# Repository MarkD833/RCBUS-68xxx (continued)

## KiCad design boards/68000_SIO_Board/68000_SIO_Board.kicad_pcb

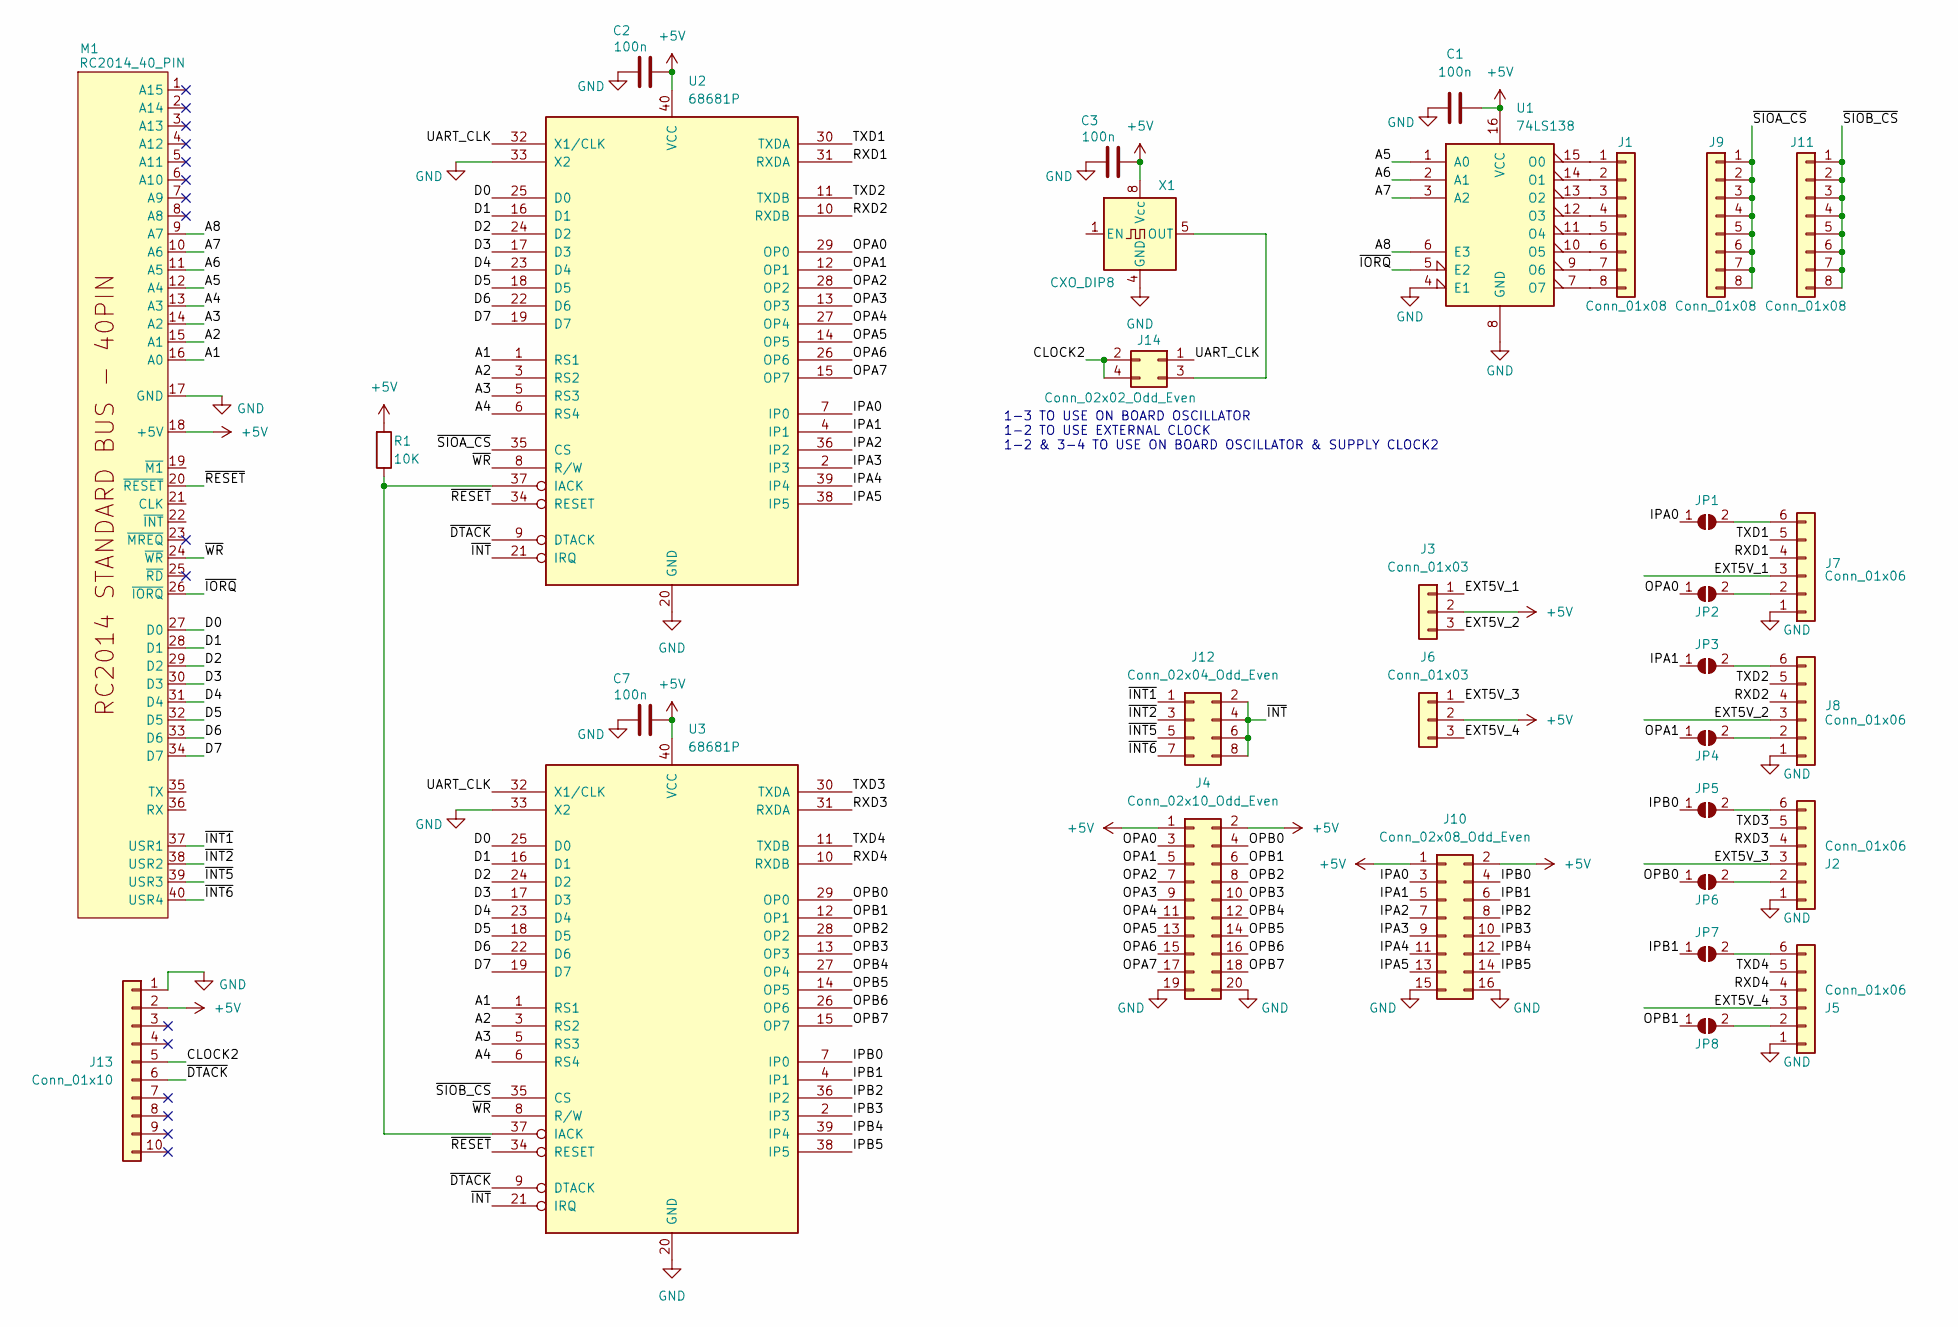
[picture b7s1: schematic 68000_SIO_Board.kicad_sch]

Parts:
C1, C2, C3, C7: 100n; C_Disc_D5.0mm_W2.5mm_P2.50mm
J1, J9, J11: Conn_01x08; PinHeader_1x08_P2.54mm_Vertical
J2, J5, J7, J8: Conn_01x06; PinSocket_1x06_P2.54mm_Horizontal
J3, J6: Conn_01x03; PinHeader_1x03_P2.54mm_Vertical
J4: Conn_02x10_Odd_Even; PinHeader_2x10_P2.54mm_Horizontal
J10: Conn_02x08_Odd_Even; PinHeader_2x08_P2.54mm_Horizontal
J12: Conn_02x04_Odd_Even; PinHeader_2x04_P2.54mm_Vertical
J13: Conn_01x10; PinHeader_1x10_P2.54mm_Vertical
J14: Conn_02x02_Odd_Even; PinHeader_2x02_P2.54mm_Vertical
JP1, JP2, JP3, JP4, JP5, JP6, JP7, JP8: SolderJumper; SolderJumper-2_P1.3mm_Open_Pad1.0x1.5mm
M1: RC2014_40_PIN; RC2014_STD_40_PIN
R1: 10K; R_Axial_DIN0207_L6.3mm_D2.5mm_P7.62mm_Horizontal
U1: 74LS138; DIP-16_W7.62mm_Socket
U2, U3: 68681P; DIP-40_W15.24mm_Socket
X1: CXO_DIP8; Oscillator_DIP-8

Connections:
+5V: C1.2, C2.2, C3.2, C7.2, J3.2, J4.1, J4.2, J6.2, J10.1, J10.2, J13.2, M1.18 (+5V), R1.2, U1.16 (VCC), U2.40 (VCC), U3.40 (VCC), X1.8 (Vcc)
/A1: M1.16 (A0), U2.1 (RS1), U3.1 (RS1)
/A2: M1.15 (A1), U2.3 (RS2), U3.3 (RS2)
/A3: M1.14 (A2), U2.5 (RS3), U3.5 (RS3)
/A4: M1.13 (A3), U2.6 (RS4), U3.6 (RS4)
/A5: M1.12 (A4), U1.1 (A0)
/A6: M1.11 (A5), U1.2 (A1)
/A7: M1.10 (A6), U1.3 (A2)
/A8: M1.9 (A7), U1.6 (E3)
/CLOCK2: J13.5, J14.2, J14.4
/D0: M1.27 (D0), U2.25 (D0), U3.25 (D0)
/D1: M1.28 (D1), U2.16 (D1), U3.16 (D1)
/D2: M1.29 (D2), U2.24 (D2), U3.24 (D2)
/D3: M1.30 (D3), U2.17 (D3), U3.17 (D3)
/D4: M1.31 (D4), U2.23 (D4), U3.23 (D4)
/D5: M1.32 (D5), U2.18 (D5), U3.18 (D5)
/D6: M1.33 (D6), U2.22 (D6), U3.22 (D6)
/D7: M1.34 (D7), U2.19 (D7), U3.19 (D7)
/EXT5V_1: J3.1, J7.3
/EXT5V_2: J3.3, J8.3
/EXT5V_3: J2.3, J6.1
/EXT5V_4: J5.3, J6.3
/IPA0: J10.3, JP1.1 (A), U2.7 (IP0)
/IPA1: J10.5, JP3.1 (A), U2.4 (IP1)
/IPA2: J10.7, U2.36 (IP2)
/IPA3: J10.9, U2.2 (IP3)
/IPA4: J10.11, U2.39 (IP4)
/IPA5: J10.13, U2.38 (IP5)
/IPB0: J10.4, JP5.1 (A), U3.7 (IP0)
/IPB1: J10.6, JP7.1 (A), U3.4 (IP1)
/IPB2: J10.8, U3.36 (IP2)
/IPB3: J10.10, U3.2 (IP3)
/IPB4: J10.12, U3.39 (IP4)
/IPB5: J10.14, U3.38 (IP5)
/OPA0: J4.3, JP2.1 (A), U2.29 (OP0)
/OPA1: J4.5, JP4.1 (A), U2.12 (OP1)
/OPA2: J4.7, U2.28 (OP2)
/OPA3: J4.9, U2.13 (OP3)
/OPA4: J4.11, U2.27 (OP4)
/OPA5: J4.13, U2.14 (OP5)
/OPA6: J4.15, U2.26 (OP6)
/OPA7: J4.17, U2.15 (OP7)
/OPB0: J4.4, JP6.1 (A), U3.29 (OP0)
/OPB1: J4.6, JP8.1 (A), U3.12 (OP1)
/OPB2: J4.8, U3.28 (OP2)
/OPB3: J4.10, U3.13 (OP3)
/OPB4: J4.12, U3.27 (OP4)
/OPB5: J4.14, U3.14 (OP5)
/OPB6: J4.16, U3.26 (OP6)
/OPB7: J4.18, U3.15 (OP7)
/RXD1: J7.4, U2.31 (RXDA)
/RXD2: J8.4, U2.10 (RXDB)
/RXD3: J2.4, U3.31 (RXDA)
/RXD4: J5.4, U3.10 (RXDB)
/TXD1: J7.5, U2.30 (TXDA)
/TXD2: J8.5, U2.11 (TXDB)
/TXD3: J2.5, U3.30 (TXDA)
/TXD4: J5.5, U3.11 (TXDB)
/UART_CLK: J14.1, U2.32 (X1/CLK), U3.32 (X1/CLK)
/~DTACK: J13.6, U2.9 (DTACK), U3.9 (DTACK)
/~INT1: J12.1, M1.37 (USR1)
/~INT2: J12.3, M1.38 (USR2)
/~INT5: J12.5, M1.39 (USR3)
/~INT6: J12.7, M1.40 (USR4)
/~INT: J12.2, J12.4, J12.6, J12.8, U2.21 (IRQ), U3.21 (IRQ)
/~IORQ: M1.26 (~IORQ), U1.5 (E2)
/~RESET: M1.20 (~RESET), U2.34 (RESET), U3.34 (RESET)
/~SIOA_CS: J9.1, J9.2, J9.3, J9.4, J9.5, J9.6, J9.7, J9.8, U2.35 (CS)
/~SIOB_CS: J11.1, J11.2, J11.3, J11.4, J11.5, J11.6, J11.7, J11.8, U3.35 (CS)
/~WR: M1.24 (~WR), U2.8 (R/W), U3.8 (R/W)
GND: C1.1, C2.1, C3.1, C7.1, J2.1, J4.19, J4.20, J5.1, J7.1, J8.1, J10.15, J10.16, J13.1, M1.17 (GND), U1.4 (E1), U1.8 (GND), U2.20 (GND), U2.33 (X2), U3.20 (GND), U3.33 (X2), X1.4 (GND)
unnamed: J1.1, U1.15 (O0)
unnamed: J1.2, U1.14 (O1)
unnamed: J1.3, U1.13 (O2)
unnamed: J1.4, U1.12 (O3)
unnamed: J1.5, U1.11 (O4)
unnamed: J1.6, U1.10 (O5)
unnamed: J1.7, U1.9 (O6)
unnamed: J1.8, U1.7 (O7)
unnamed: J2.2, JP6.2 (B)
unnamed: J2.6, JP5.2 (B)
unnamed: J5.2, JP8.2 (B)
unnamed: J5.6, JP7.2 (B)
unnamed: J7.2, JP2.2 (B)
unnamed: J7.6, JP1.2 (B)
unnamed: J8.2, JP4.2 (B)
unnamed: J8.6, JP3.2 (B)
unnamed: J14.3, X1.5 (OUT)
unnamed: R1.1, U2.37 (IACK), U3.37 (IACK)

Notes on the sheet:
1-3 TO USE ON BOARD OSCILLATOR 1-2 TO USE EXTERNAL CLOCK 1-2 & 3-4 TO USE ON BOARD OSCILLATOR & SUPPLY CLOCK2

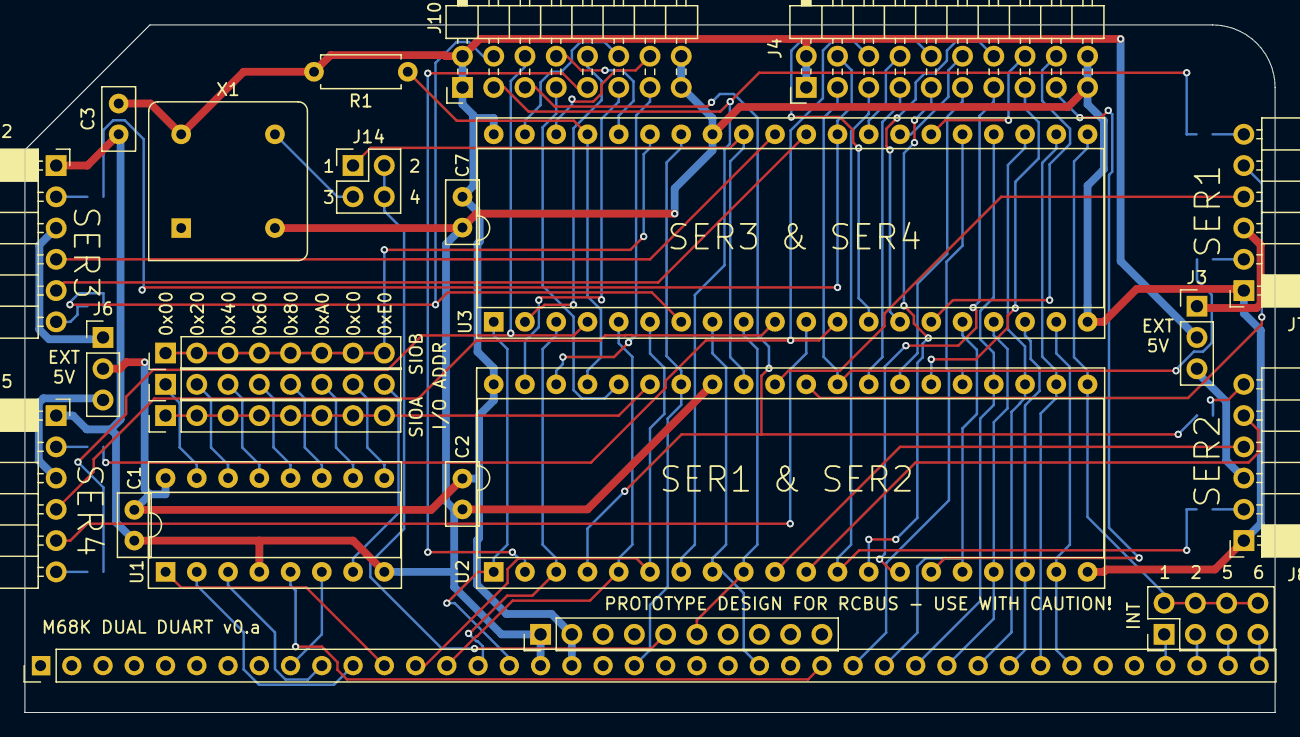
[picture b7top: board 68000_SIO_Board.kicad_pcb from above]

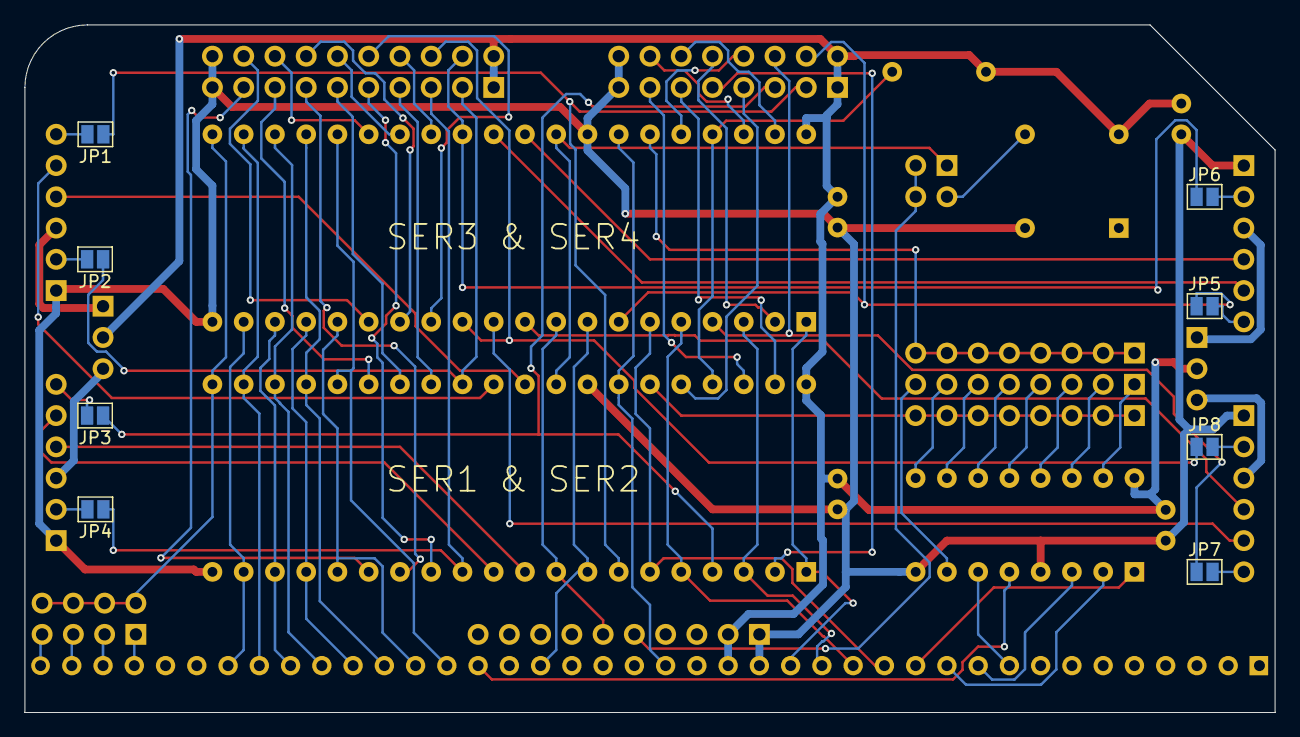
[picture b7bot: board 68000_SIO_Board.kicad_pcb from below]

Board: 2 copper layers, 101.6 x 55.9 mm, 32 parts (8 on the bottom side), 89 nets.

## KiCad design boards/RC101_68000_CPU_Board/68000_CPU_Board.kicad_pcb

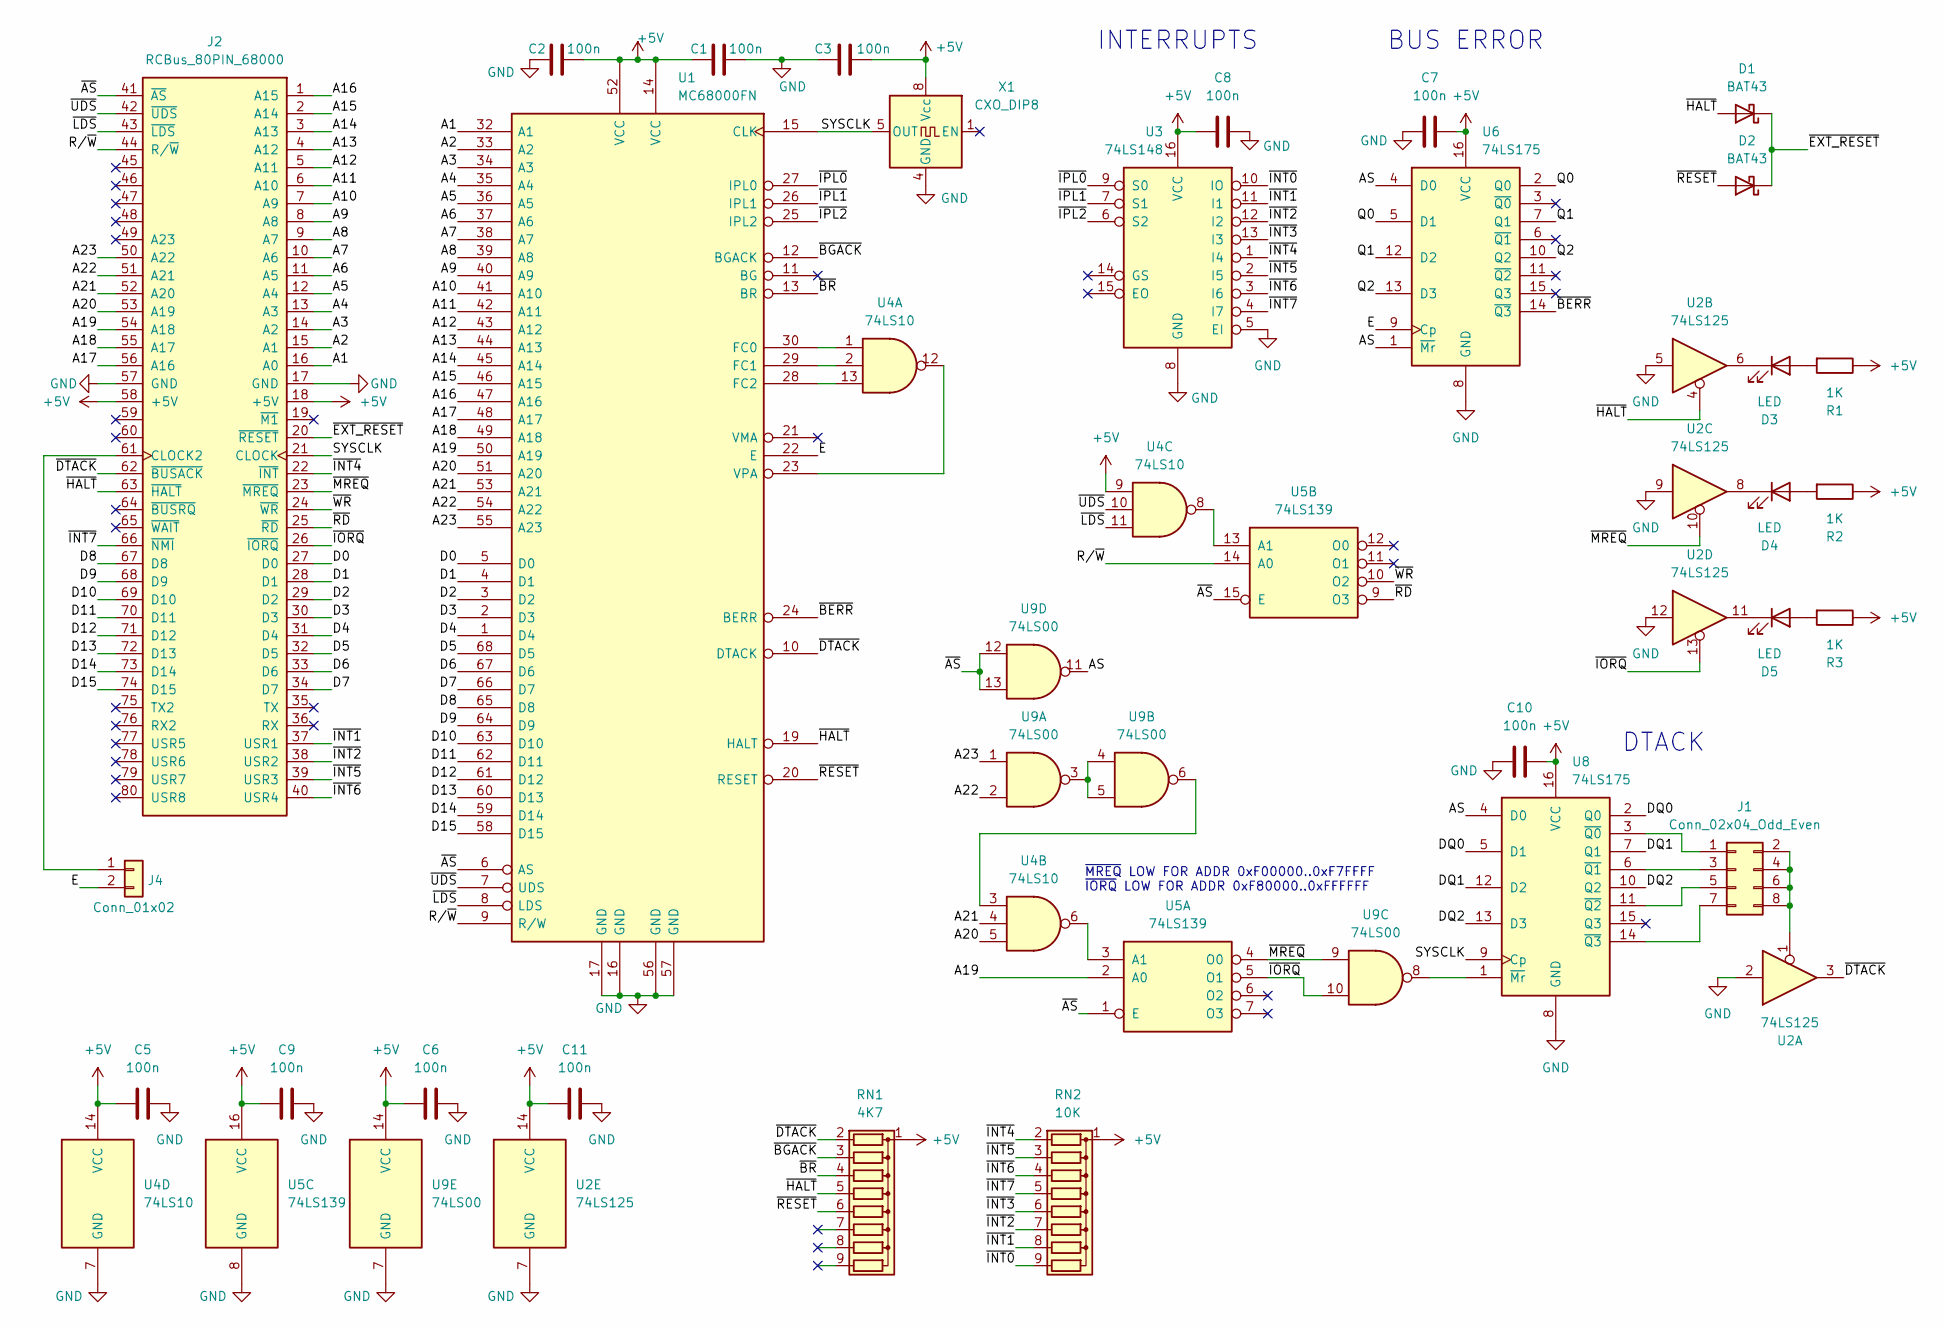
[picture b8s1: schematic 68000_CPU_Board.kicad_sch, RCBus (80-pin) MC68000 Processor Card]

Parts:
C1, C2, C3, C5, C6, C7, C8, C9, C10, C11: 100n; C_Disc_D5.0mm_W2.5mm_P2.50mm
D1, D2: BAT43; D_DO-35_SOD27_P7.62mm_Horizontal
D3, D4, D5: LED; LED_D3.0mm
J1: Conn_02x04_Odd_Even; PinHeader_2x04_P2.54mm_Vertical
J2: RCBus_80PIN_68000; RCBus_80p_Medium
J4: Conn_01x02; PinHeader_1x02_P2.54mm_Vertical
R1, R2, R3: 1K; R_Axial_DIN0207_L6.3mm_D2.5mm_P7.62mm_Horizontal
RN1: 4K7; R_Array_SIP9
RN2: 10K; R_Array_SIP9
U1: MC68000FN; PLCC-68_THT-Socket
U2: 74LS125; DIP-14_W7.62mm_Socket
U3: 74LS148; DIP-16_W7.62mm_Socket
U4: 74LS10; DIP-14_W7.62mm_Socket
U5: 74LS139; DIP-16_W7.62mm_Socket
U6, U8: 74LS175; DIP-16_W7.62mm_Socket
U9: 74LS00; DIP-14_W7.62mm_Socket
X1: CXO_DIP8; Oscillator_DIP-8

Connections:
+5V: C1.1, C2.2, C3.2, C5.1, C6.1, C7.2, C8.1, C9.1, C10.2, C11.1, J2.18 (+5V), J2.58 (+5V), R1.1, R2.1, R3.1, RN1.1 (common), RN2.1 (common), U1.14 (VCC), U1.52 (VCC), U2.14 (VCC), U3.16 (VCC), U4.9, U4.14 (VCC), U5.16 (VCC), U6.16 (VCC), U8.16 (VCC), U9.14 (VCC), X1.8 (Vcc)
/A1: J2.16 (A0), U1.32 (A1)
/A2: J2.15 (A1), U1.33 (A2)
/A3: J2.14 (A2), U1.34 (A3)
/A4: J2.13 (A3), U1.35 (A4)
/A5: J2.12 (A4), U1.36 (A5)
/A6: J2.11 (A5), U1.37 (A6)
/A7: J2.10 (A6), U1.38 (A7)
/A8: J2.9 (A7), U1.39 (A8)
/A9: J2.8 (A8), U1.40 (A9)
/A10: J2.7 (A9), U1.41 (A10)
/A11: J2.6 (A10), U1.42 (A11)
/A12: J2.5 (A11), U1.43 (A12)
/A13: J2.4 (A12), U1.44 (A13)
/A14: J2.3 (A13), U1.45 (A14)
/A15: J2.2 (A14), U1.46 (A15)
/A16: J2.1 (A15), U1.47 (A16)
/A17: J2.56 (A16), U1.48 (A17)
/A18: J2.55 (A17), U1.49 (A18)
/A19: J2.54 (A18), U1.50 (A19), U5.2 (A0)
/A20: J2.53 (A19), U1.51 (A20), U4.5
/A21: J2.52 (A20), U1.53 (A21), U4.4
/A22: J2.51 (A21), U1.54 (A22), U9.2
/A23: J2.50 (A22), U1.55 (A23), U9.1
/AS: U6.1 (~Mr), U6.4 (D0), U8.4 (D0), U9.11
/D0: J2.27 (D0), U1.5 (D0)
/D1: J2.28 (D1), U1.4 (D1)
/D2: J2.29 (D2), U1.3 (D2)
/D3: J2.30 (D3), U1.2 (D3)
/D4: J2.31 (D4), U1.1 (D4)
/D5: J2.32 (D5), U1.68 (D5)
/D6: J2.33 (D6), U1.67 (D6)
/D7: J2.34 (D7), U1.66 (D7)
/D8: J2.67 (D8), U1.65 (D8)
/D9: J2.68 (D9), U1.64 (D9)
/D10: J2.69 (D10), U1.63 (D10)
/D11: J2.70 (D11), U1.62 (D11)
/D12: J2.71 (D12), U1.61 (D12)
/D13: J2.72 (D13), U1.60 (D13)
/D14: J2.73 (D14), U1.59 (D14)
/D15: J2.74 (D15), U1.58 (D15)
/DQ0: U8.2 (Q0), U8.5 (D1)
/DQ1: U8.7 (Q1), U8.12 (D2)
/DQ2: U8.10 (Q2), U8.13 (D3)
/E: J4.2, U1.22 (E), U6.9 (Cp)
/Q0: U6.2 (Q0), U6.5 (D1)
/Q1: U6.7 (Q1), U6.12 (D2)
/Q2: U6.10 (Q2), U6.13 (D3)
/R/~W: J2.44 (R/~W), U1.9 (R/W), U5.14 (A0)
/SYSCLK: J2.21 (CLOCK), U1.15 (CLK), U8.9 (Cp), X1.5 (OUT)
/~AS: J2.41 (~AS), U1.6 (AS), U5.1 (E), U5.15 (E), U9.12, U9.13
/~BERR: U1.24 (BERR), U6.14 (~Q3)
/~BGACK: RN1.3 (R2), U1.12 (BGACK)
/~BR: RN1.4 (R3), U1.13 (BR)
/~DTACK: J2.62 (~BUSACK), RN1.2 (R1), U1.10 (DTACK), U2.3
/~EXT_RESET: D1.1 (K), D2.1 (K), J2.20 (~RESET)
/~HALT: D1.2 (A), J2.63 (~HALT), RN1.5 (R4), U1.19 (HALT), U2.4
/~INT0: RN2.9 (R8), U3.10 (IO)
/~INT1: J2.37 (USR1), RN2.8 (R7), U3.11 (I1)
/~INT2: J2.38 (USR2), RN2.7 (R6), U3.12 (I2)
/~INT3: RN2.6 (R5), U3.13 (I3)
/~INT4: J2.22 (~INT), RN2.2 (R1), U3.1 (I4)
/~INT5: J2.39 (USR3), RN2.3 (R2), U3.2 (I5)
/~INT6: J2.40 (USR4), RN2.4 (R3), U3.3 (I6)
/~INT7: J2.66 (~NMI), RN2.5 (R4), U3.4 (I7)
/~IORQ: J2.26 (~IORQ), U2.13, U5.5 (O1), U9.10
/~IPL0: U1.27 (IPL0), U3.9 (S0)
/~IPL1: U1.26 (IPL1), U3.7 (S1)
/~IPL2: U1.25 (IPL2), U3.6 (S2)
/~LDS: J2.43 (~LDS), U1.8 (LDS), U4.11
/~MREQ: J2.23 (~MREQ), U2.10, U5.4 (O0), U9.9
/~RD: J2.25 (~RD), U5.9 (O3)
/~RESET: D2.2 (A), RN1.6 (R5), U1.20 (RESET)
/~UDS: J2.42 (~UDS), U1.7 (UDS), U4.10
/~WR: J2.24 (~WR), U5.10 (O2)
GND: C1.2, C2.1, C3.1, C5.2, C6.2, C7.1, C8.2, C9.2, C10.1, C11.2, J2.17 (GND), J2.57 (GND), U1.16 (GND), U1.17 (GND), U1.56 (GND), U1.57 (GND), U2.2, U2.5, U2.7 (GND), U2.9, U2.12, U3.5 (EI), U3.8 (GND), U4.7 (GND), U5.8 (GND), U6.8 (GND), U8.8 (GND), U9.7 (GND), X1.4 (GND)
unnamed: D3.2 (A), R1.2
unnamed: D3.1 (K), U2.6
unnamed: D4.2 (A), R2.2
unnamed: D4.1 (K), U2.8
unnamed: D5.2 (A), R3.2
unnamed: D5.1 (K), U2.11
unnamed: J1.1, U8.3 (~Q0)
unnamed: J1.2, J1.4, J1.6, J1.8, U2.1
unnamed: J1.3, U8.6 (~Q1)
unnamed: J1.5, U8.11 (~Q2)
unnamed: J1.7, U8.14 (~Q3)
unnamed: J2.61 (CLOCK2), J4.1
unnamed: U1.30 (FC0), U4.1
unnamed: U1.29 (FC1), U4.2
unnamed: U1.28 (FC2), U4.13
unnamed: U1.23 (VPA), U4.12
unnamed: U4.3, U9.6
unnamed: U4.6, U5.3 (A1)
unnamed: U4.8, U5.13 (A1)
unnamed: U8.1 (~Mr), U9.8
unnamed: U9.3, U9.4, U9.5

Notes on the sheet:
INTERRUPTS
DTACK
~{MREQ} LOW FOR ADDR 0xF00000..0xF7FFFF ~{IORQ} LOW FOR ADDR 0xF80000..0xFFFFFF
BUS ERROR

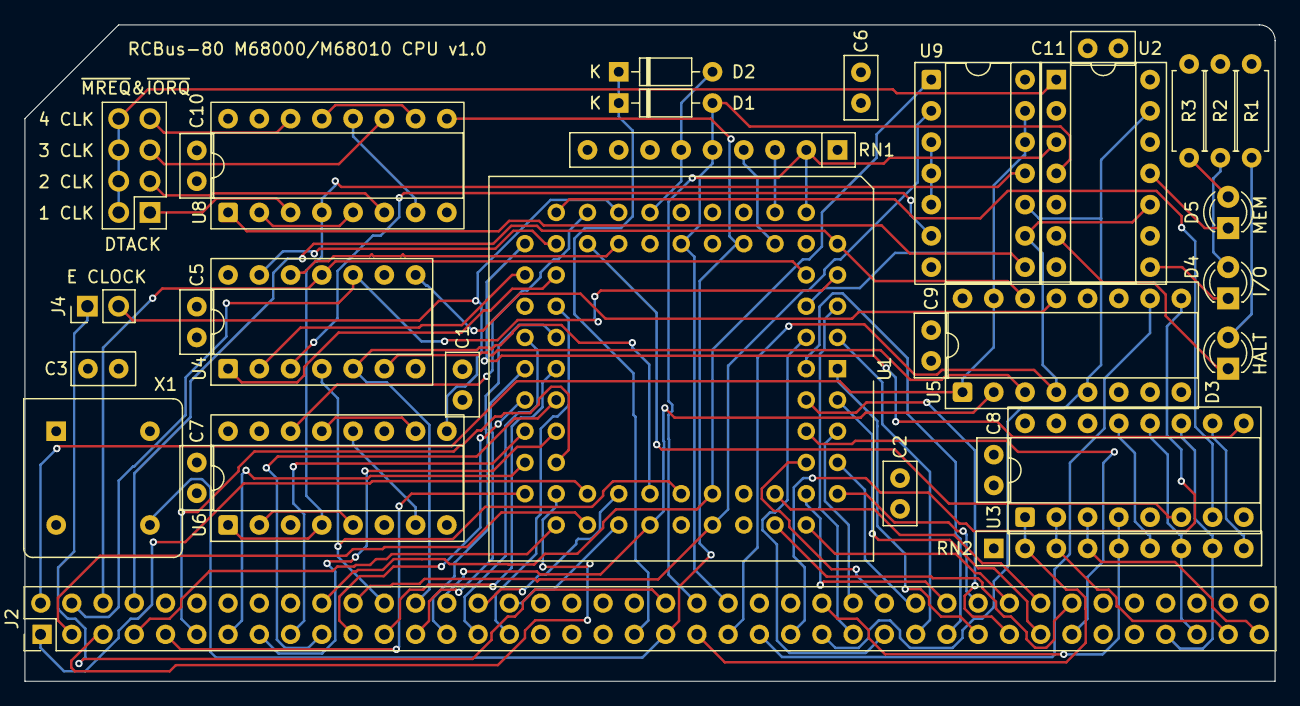
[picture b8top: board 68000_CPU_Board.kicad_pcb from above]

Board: 4 copper layers, 101.6 x 53.3 mm, 32 parts (0 on the bottom side), 97 nets.
